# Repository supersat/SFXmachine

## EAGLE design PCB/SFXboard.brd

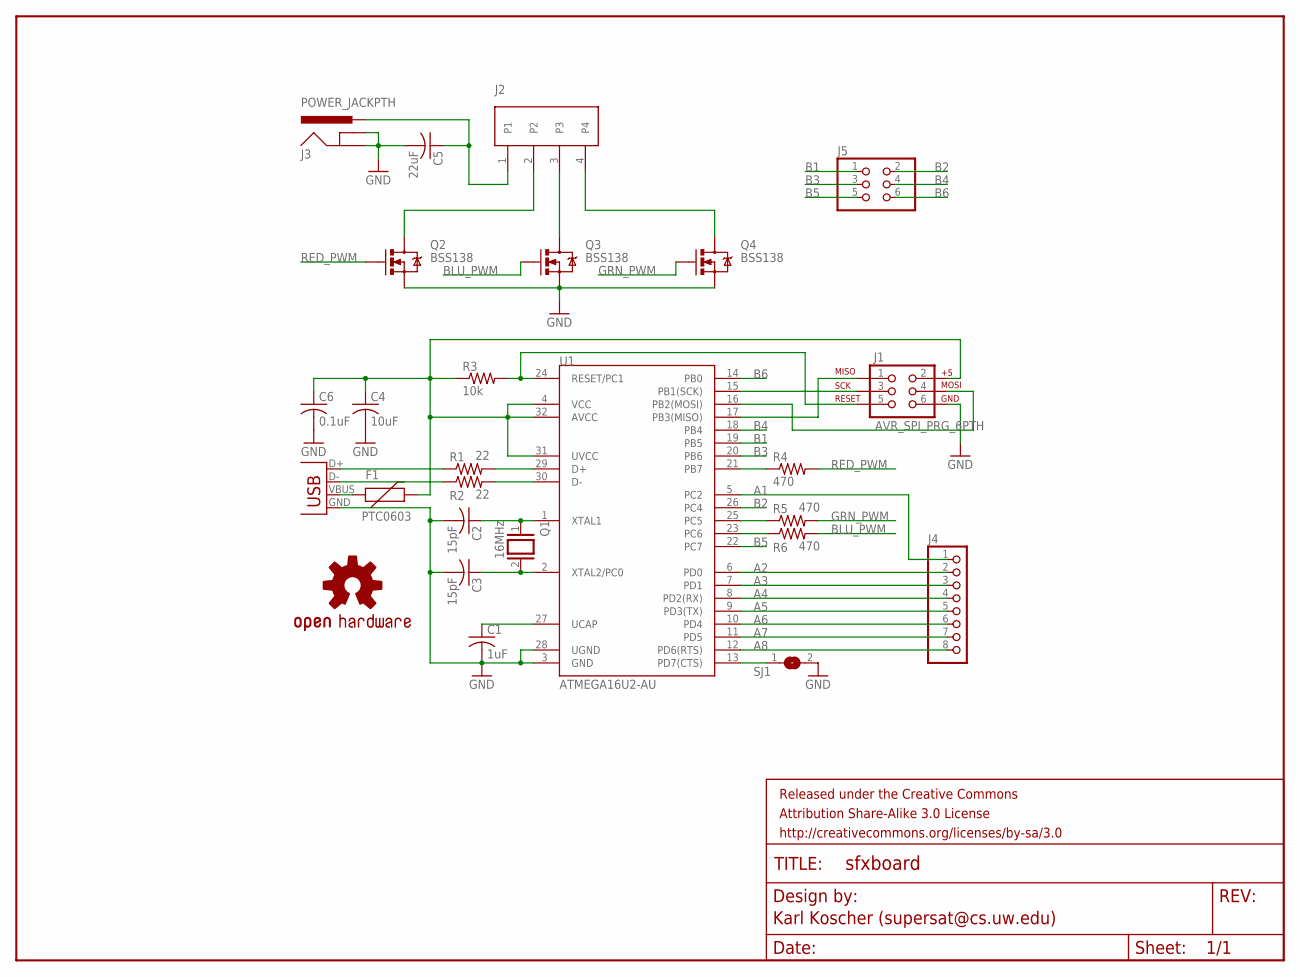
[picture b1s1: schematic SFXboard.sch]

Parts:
C1: 1uF; C0603
C2, C3: 15pF; C0603
C4: 10uF; C0805
C5: 22uF; C0805
C6: 0.1uF; C0402
F1: PTC0603; 0603
FRAME1: FRAME-LETTER; CREATIVE_COMMONS
J1: AVR_SPI_PRG_6PTH; 2X3
J2: TERMBLOCK4POS; TERMBLOCK4P
J3: POWER_JACKPTH; POWER_JACK_PTH
J4: PINHD-1X8; 1X08
J5: PINHD-2X3; 2X03
Q1: 16MHz; QS
Q2, Q3, Q4: BSS138; SOT23-3
R1, R2: 22; R0603
R3: 10k; R0603
R4, R5, R6: 470; R0603
SJ1: SJ
U1: ATMEGA16U2-AU; TQFP32-08
U$2: OSHW-LOGOS; OSHW-LOGO-S
X1: USBSMD; USB-MINIB

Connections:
A1: J4.1, U1.5 (PC2)
A2: J4.2, U1.6 (PD0)
A3: J4.3, U1.7 (PD1)
A4: J4.4, U1.8 (PD2(RX))
A5: J4.5, U1.9 (PD3(TX))
A6: J4.6, U1.10 (PD4)
A7: J4.7, U1.11 (PD5)
A8: J4.8, U1.12 (PD6(RTS))
B: R6.1, U1.23 (PC6)
B1: J5.1, U1.19 (PB5)
B2: J5.2, U1.26 (PC4)
B3: J5.3, U1.20 (PB6)
B4: J5.4, U1.18 (PB4)
B5: J5.5, U1.22 (PC7)
B6: J5.6, U1.14 (PB0)
BLU_PWM: Q3.1 (G), R6.2
G: R5.1, U1.25 (PC5)
GND: C1.2, C2.2, C3.2, C4.2, C5.2, C6.2, J1.6, J3.GND, J3.GNDBREAK, Q2.2 (S), Q3.2 (S), Q4.2 (S), SJ1.2, U1.3 (GND), U1.28 (UGND), X1.GND
GRN_PWM: Q4.1 (G), R5.2
unnamed: C1.1, U1.27 (UCAP)
unnamed: F1.1, X1.VBUS
unnamed: R1.1, X1.D+
unnamed: R2.1, X1.D-
unnamed: R1.2, U1.29 (D+)
unnamed: R2.2, U1.30 (D-)
unnamed: J1.5, R3.2, U1.24 (RESET/PC1)
unnamed: C2.1, Q1.1, U1.1 (XTAL1)
unnamed: C3.1, Q1.2, U1.2 (XTAL2/PC0)
unnamed: J2.2, Q2.3 (D)
unnamed: J1.3, U1.15 (PB1(SCK))
unnamed: J1.1, U1.17 (PB3(MISO))
unnamed: J1.4, U1.16 (PB2(MOSI))
unnamed: J2.3, Q3.3 (D)
unnamed: J2.4, Q4.3 (D)
unnamed: C5.1, J2.1, J3.PWR
unnamed: SJ1.1, U1.13 (PD7(CTS))
unnamed: C4.1, C6.1, F1.2, J1.2, R3.1, U1.4 (VCC), U1.31 (UVCC), U1.32 (AVCC)
R: R4.1, U1.21 (PB7)
RED_PWM: Q2.1 (G), R4.2

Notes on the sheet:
Karl Koscher (supersat@cs.uw.edu)

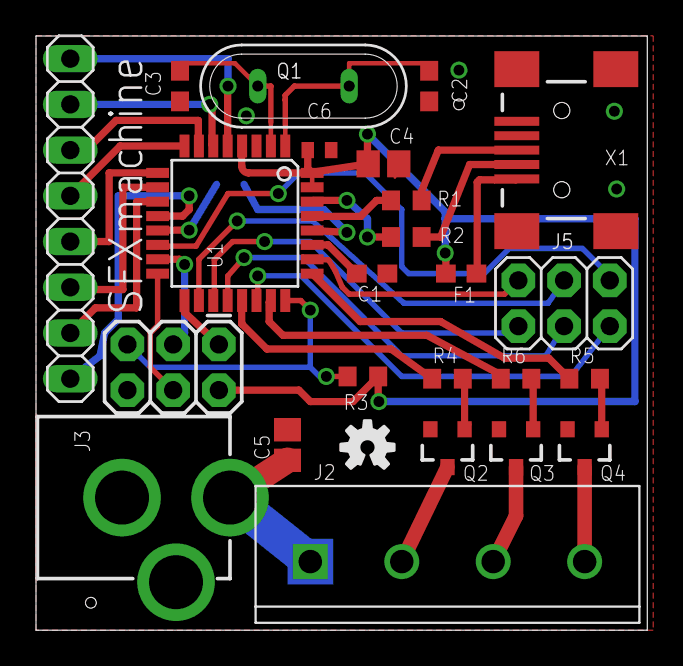
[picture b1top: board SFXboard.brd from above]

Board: 2 copper layers, 34.0 x 33.0 mm, 27 parts (1 on the bottom side), 39 nets.

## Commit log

2012-09-16 Add SFXboard
2012-09-16 SFXboard library
2012-09-16 SFXboard layout
2012-09-16 Layout checkpoint
2012-09-16 IT IS DONE
2012-09-16 Smaller OSHW logo
2012-09-23 Move PCB into its own directory
2012-09-27 Add firmware
2012-09-29 Firmware almost works
2012-10-02 Bring everything up to date
2012-10-02 Fixed firmware
2012-10-02 Typo fix
2012-10-06 Fix potential CKDIV issue
2012-10-09 Add BOM
2012-10-28 Begin working on better power filtering, misc enhancements
2012-10-31 Circuit improvements, but not yet complete
2012-10-31 Cleanup for release
2012-11-23 New board rev with all GPIO brought out
2012-11-28 Final tweaks for rev2

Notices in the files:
parts and their libraries:
SparkFun-DigitalIC: Licensing: CC v3.0 Share-Alike You are welcome to use this library for commercial purposes.
SparkFun-Aesthetics: Released under the Creative Commons Attribution Share-Alike 3.0 License
SparkFun-Aesthetics: http://creativecommons.org/licenses/by-sa/3.0
